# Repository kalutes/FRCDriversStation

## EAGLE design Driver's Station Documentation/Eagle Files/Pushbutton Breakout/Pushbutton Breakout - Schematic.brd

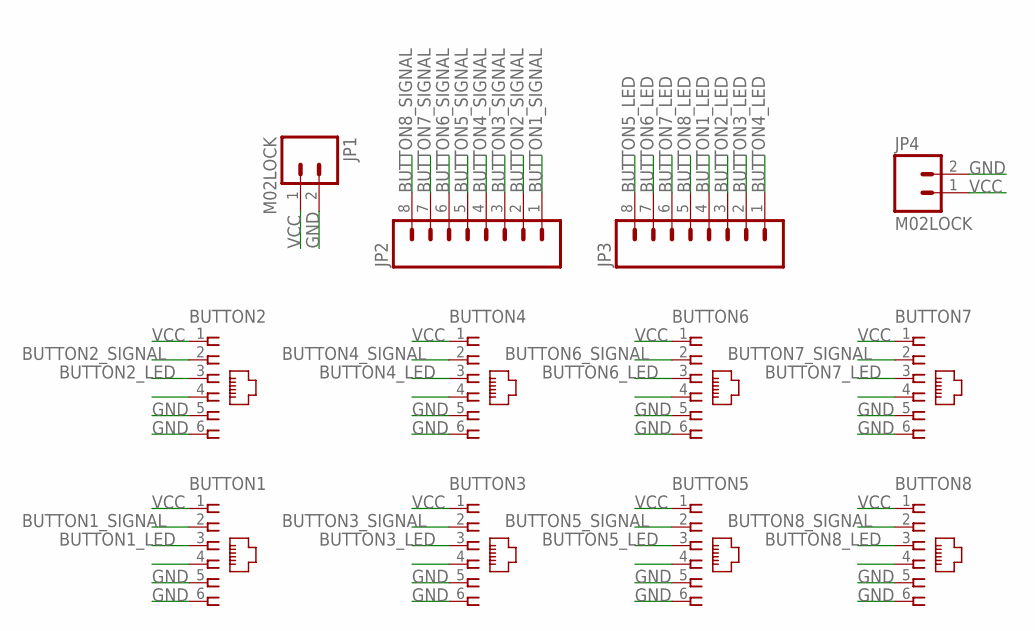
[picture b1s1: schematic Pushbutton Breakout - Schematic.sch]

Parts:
BUTTON1, BUTTON2, BUTTON3, BUTTON4, BUTTON5, BUTTON6, BUTTON7, BUTTON8: 555165-1
JP1, JP4: M02LOCK; 1X02_LOCK
JP2, JP3: M08LOCK; 1X08_LOCK

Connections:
BUTTON1_LED: BUTTON1.3, JP3.4
BUTTON1_SIGNAL: BUTTON1.2, JP2.1
BUTTON2_LED: BUTTON2.3, JP3.3
BUTTON2_SIGNAL: BUTTON2.2, JP2.2
BUTTON3_LED: BUTTON3.3, JP3.2
BUTTON3_SIGNAL: BUTTON3.2, JP2.3
BUTTON4_LED: BUTTON4.3, JP3.1
BUTTON4_SIGNAL: BUTTON4.2, JP2.4
BUTTON5_LED: BUTTON5.3, JP3.8
BUTTON5_SIGNAL: BUTTON5.2, JP2.5
BUTTON6_LED: BUTTON6.3, JP3.7
BUTTON6_SIGNAL: BUTTON6.2, JP2.6
BUTTON7_LED: BUTTON7.3, JP3.6
BUTTON7_SIGNAL: BUTTON7.2, JP2.7
BUTTON8_LED: BUTTON8.3, JP3.5
BUTTON8_SIGNAL: BUTTON8.2, JP2.8
GND: BUTTON1.5, BUTTON1.6, BUTTON2.5, BUTTON2.6, BUTTON3.5, BUTTON3.6, BUTTON4.5, BUTTON4.6, BUTTON5.5, BUTTON5.6, BUTTON6.5, BUTTON6.6, BUTTON7.5, BUTTON7.6, BUTTON8.5, BUTTON8.6, JP1.2, JP4.2
VCC: BUTTON1.1, BUTTON2.1, BUTTON3.1, BUTTON4.1, BUTTON5.1, BUTTON6.1, BUTTON7.1, BUTTON8.1, JP1.1, JP4.1

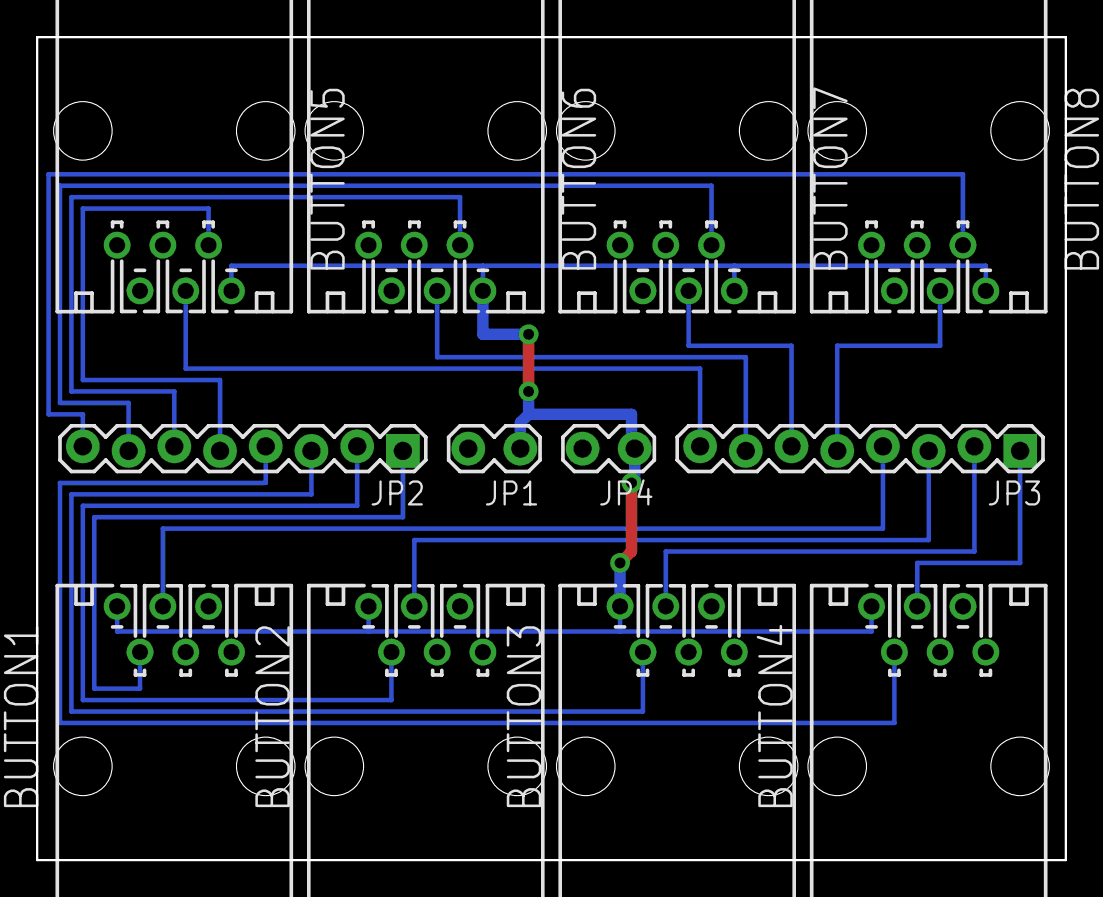
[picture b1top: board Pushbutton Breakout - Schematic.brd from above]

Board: 2 copper layers, 57.1 x 45.7 mm, 12 parts (0 on the bottom side), 18 nets.

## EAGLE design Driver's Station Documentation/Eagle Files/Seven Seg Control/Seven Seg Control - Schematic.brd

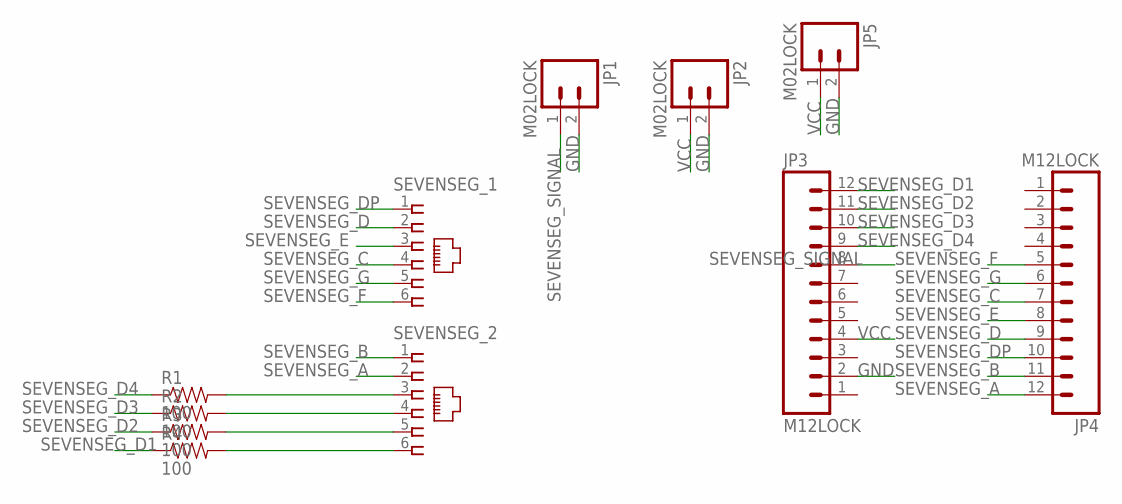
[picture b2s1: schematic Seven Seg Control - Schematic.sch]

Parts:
JP1, JP2, JP5: M02LOCK; 1X02_LOCK
JP3, JP4: M12LOCK; 1X12_LOCK
R1, R2, R3, R4: 100; 0603-RES
SEVENSEG_1, SEVENSEG_2: 555165-1

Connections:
GND: JP1.2, JP2.2, JP3.2, JP5.2
unnamed: R4.2, SEVENSEG_2.6
unnamed: R2.2, SEVENSEG_2.4
unnamed: R3.2, SEVENSEG_2.5
unnamed: R1.2, SEVENSEG_2.3
SEVENSEG_A: JP4.12, SEVENSEG_2.2
SEVENSEG_B: JP4.11, SEVENSEG_2.1
SEVENSEG_C: JP4.7, SEVENSEG_1.4
SEVENSEG_D: JP4.9, SEVENSEG_1.2
SEVENSEG_D1: JP3.12, R4.1
SEVENSEG_D2: JP3.11, R3.1
SEVENSEG_D3: JP3.10, R2.1
SEVENSEG_D4: JP3.9, R1.1
SEVENSEG_DP: JP4.10, SEVENSEG_1.1
SEVENSEG_E: JP4.8, SEVENSEG_1.3
SEVENSEG_F: JP4.5, SEVENSEG_1.6
SEVENSEG_G: JP4.6, SEVENSEG_1.5
SEVENSEG_SIGNAL: JP1.1, JP3.8
VCC: JP2.1, JP3.4, JP5.1

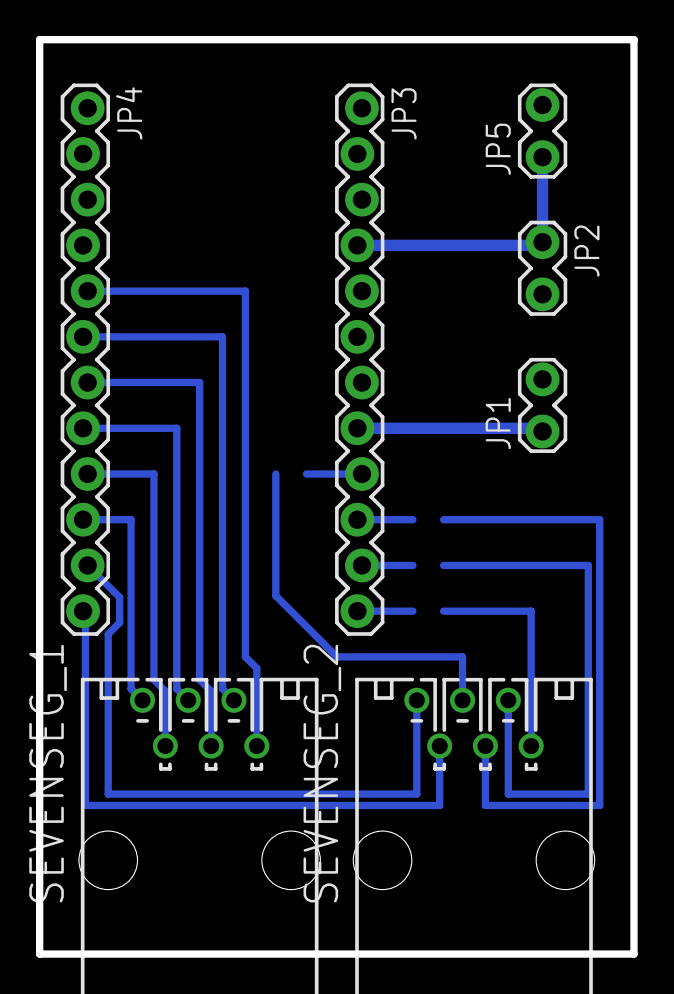
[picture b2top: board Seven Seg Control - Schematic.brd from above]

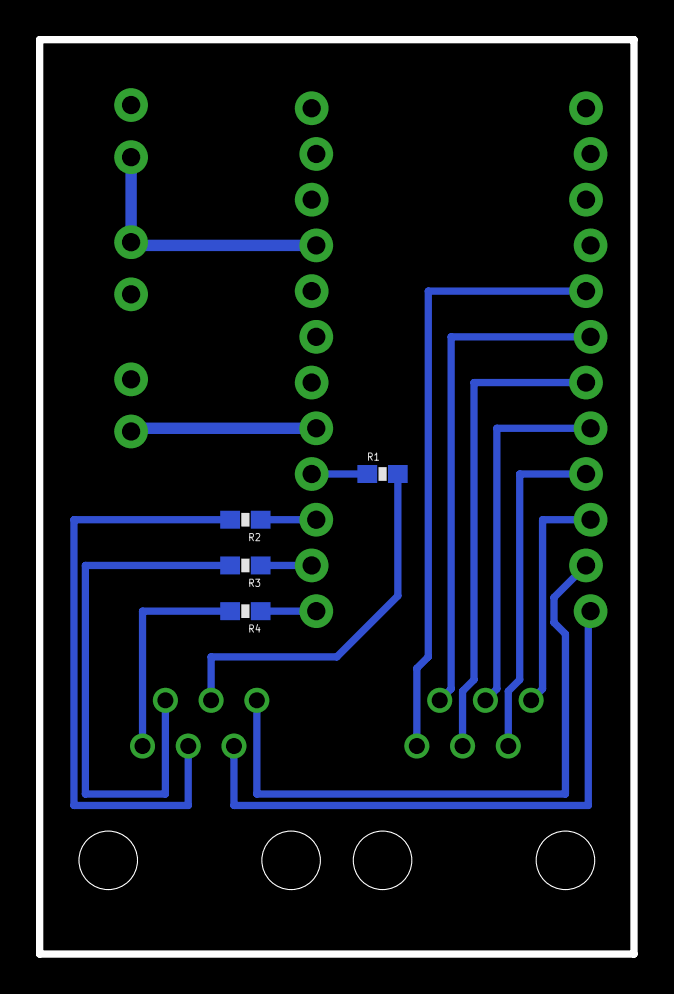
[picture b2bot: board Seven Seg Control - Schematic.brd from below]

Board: 2 copper layers, 33.0 x 50.8 mm, 11 parts (4 on the bottom side), 19 nets.

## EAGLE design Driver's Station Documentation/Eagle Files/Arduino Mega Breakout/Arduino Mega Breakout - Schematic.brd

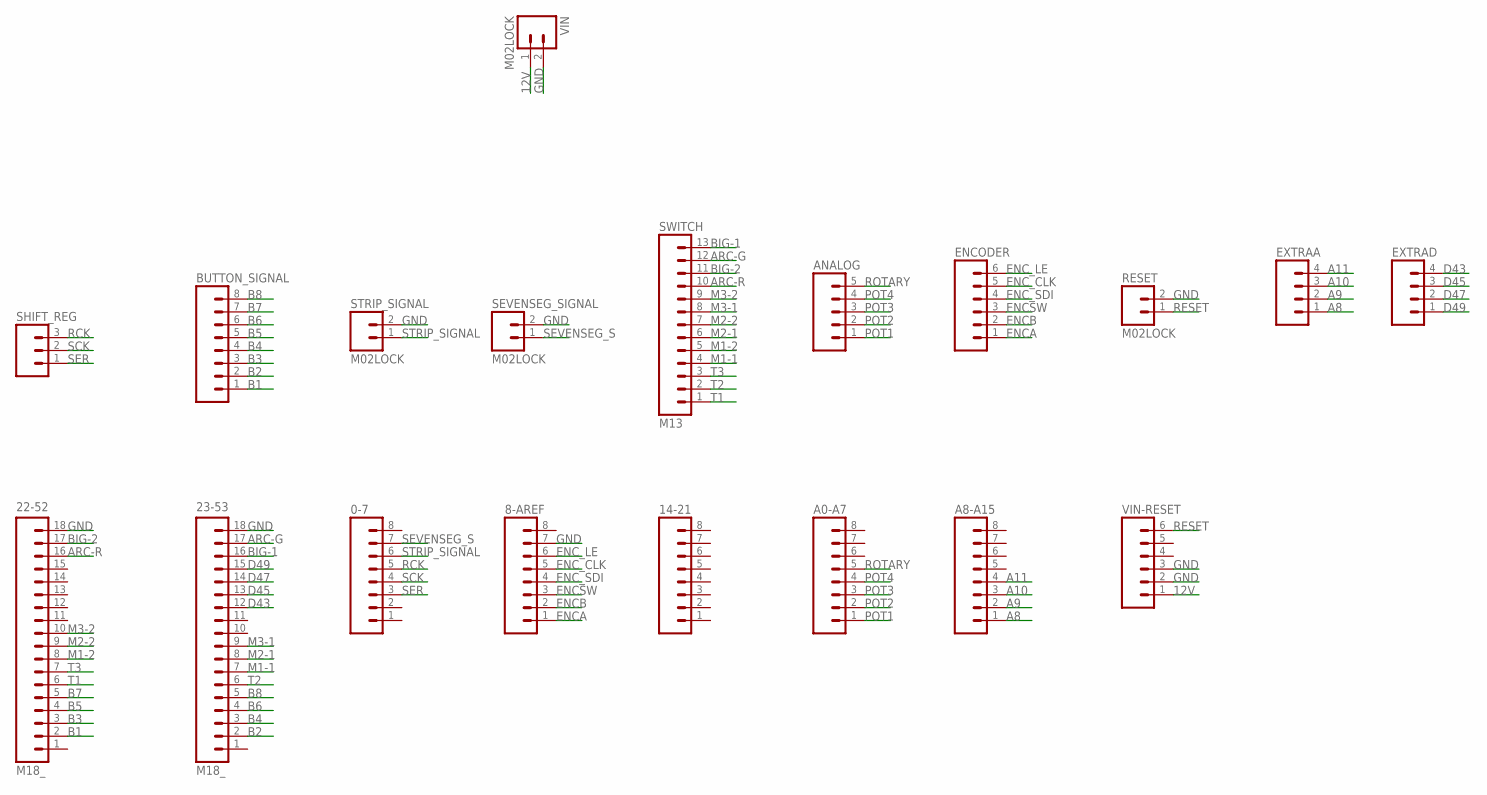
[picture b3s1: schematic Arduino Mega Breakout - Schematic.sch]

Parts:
0-7, 8-AREF, 14-21: M08LOCK; 1X08_LOCK
22-52, 23-53: M18_; 1X18
A0-A7, A8-A15: M08LOCK; 1X08_LOCK
ANALOG: M05LOCK; 1X05_LOCK
BUTTON_SIGNAL: M08; 1X08_PIN1_NO_SILK
ENCODER: M06LOCK; 1X06_LOCK
EXTRAA: M04LOCK; 1X04_LOCK
EXTRAD: M04PTH; 1X04
RESET: M02LOCK; 1X02_LOCK
SEVENSEG_SIGNAL: M02LOCK; 1X02_LOCK
SHIFT_REG: M03LOCK; 1X03_LOCK
STRIP_SIGNAL: M02LOCK; 1X02_LOCK
SWITCH: M13; 1X13
VIN: M02LOCK; 1X02_LOCK
VIN-RESET: M06LOCK; 1X06_LOCK

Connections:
12V: VIN.1, VIN-RESET.1
A8: A8-A15.1, EXTRAA.1
A9: A8-A15.2, EXTRAA.2
A10: A8-A15.3, EXTRAA.3
A11: A8-A15.4, EXTRAA.4
ARC-G: 23-53.17, SWITCH.12
ARC-R: 22-52.16, SWITCH.10
B1: 22-52.2, BUTTON_SIGNAL.1
B2: 23-53.2, BUTTON_SIGNAL.2
B3: 22-52.3, BUTTON_SIGNAL.3
B4: 23-53.3, BUTTON_SIGNAL.4
B5: 22-52.4, BUTTON_SIGNAL.5
B6: 23-53.4, BUTTON_SIGNAL.6
B7: 22-52.5, BUTTON_SIGNAL.7
B8: 23-53.5, BUTTON_SIGNAL.8
BIG-1: 23-53.16, SWITCH.13
BIG-2: 22-52.17, SWITCH.11
D43: 23-53.12, EXTRAD.4
D45: 23-53.13, EXTRAD.3
D47: 23-53.14, EXTRAD.2
D49: 23-53.15, EXTRAD.1
ENCA: 8-AREF.1, ENCODER.1
ENCB: 8-AREF.2, ENCODER.2
ENCSW: 8-AREF.3, ENCODER.3
ENC_CLK: 8-AREF.5, ENCODER.5
ENC_LE: 8-AREF.6, ENCODER.6
ENC_SDI: 8-AREF.4, ENCODER.4
GND: 8-AREF.7, 22-52.18, 23-53.18, RESET.2, SEVENSEG_SIGNAL.2, STRIP_SIGNAL.2, VIN.2, VIN-RESET.2, VIN-RESET.3
M1-1: 23-53.7, SWITCH.4
M1-2: 22-52.8, SWITCH.5
M2-1: 23-53.8, SWITCH.6
M2-2: 22-52.9, SWITCH.7
M3-1: 23-53.9, SWITCH.8
M3-2: 22-52.10, SWITCH.9
POT1: A0-A7.1, ANALOG.1
POT2: A0-A7.2, ANALOG.2
POT3: A0-A7.3, ANALOG.3
POT4: A0-A7.4, ANALOG.4
RCK: 0-7.5, SHIFT_REG.3
RESET: RESET.1, VIN-RESET.6
ROTARY: A0-A7.5, ANALOG.5
SCK: 0-7.4, SHIFT_REG.2
SER: 0-7.3, SHIFT_REG.1
SEVENSEG_S: 0-7.7, SEVENSEG_SIGNAL.1
STRIP_SIGNAL: 0-7.6, STRIP_SIGNAL.1
T1: 22-52.6, SWITCH.1
T2: 23-53.6, SWITCH.2
T3: 22-52.7, SWITCH.3

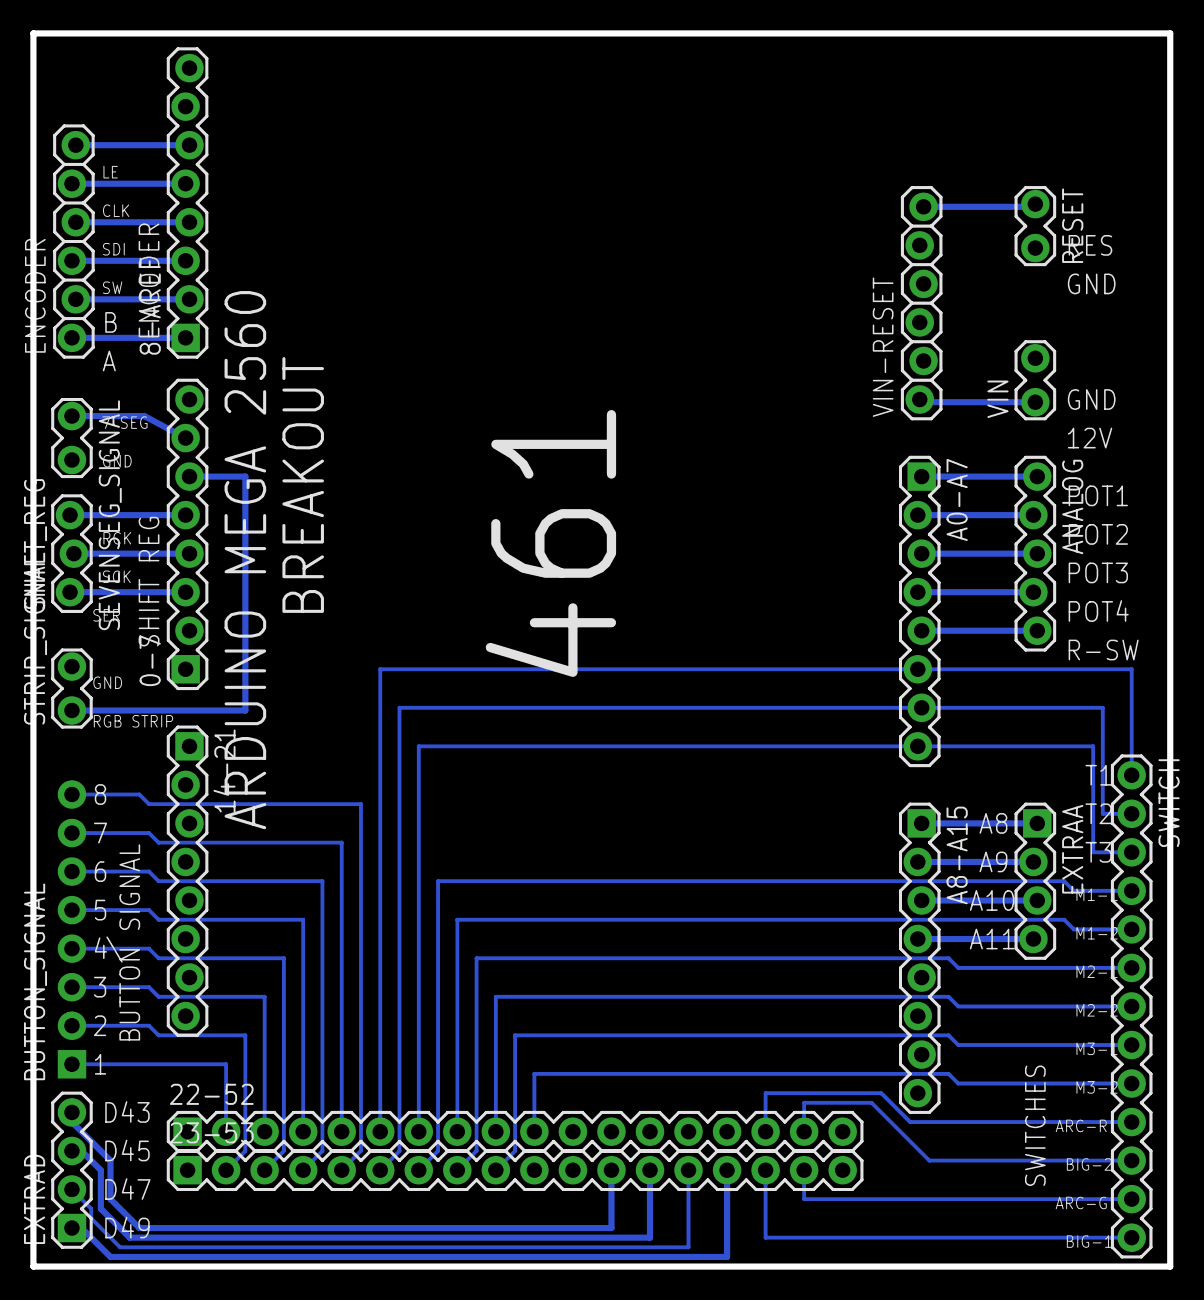
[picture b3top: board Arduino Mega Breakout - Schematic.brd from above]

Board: 2 copper layers, 74.9 x 81.3 mm, 19 parts (0 on the bottom side), 48 nets.

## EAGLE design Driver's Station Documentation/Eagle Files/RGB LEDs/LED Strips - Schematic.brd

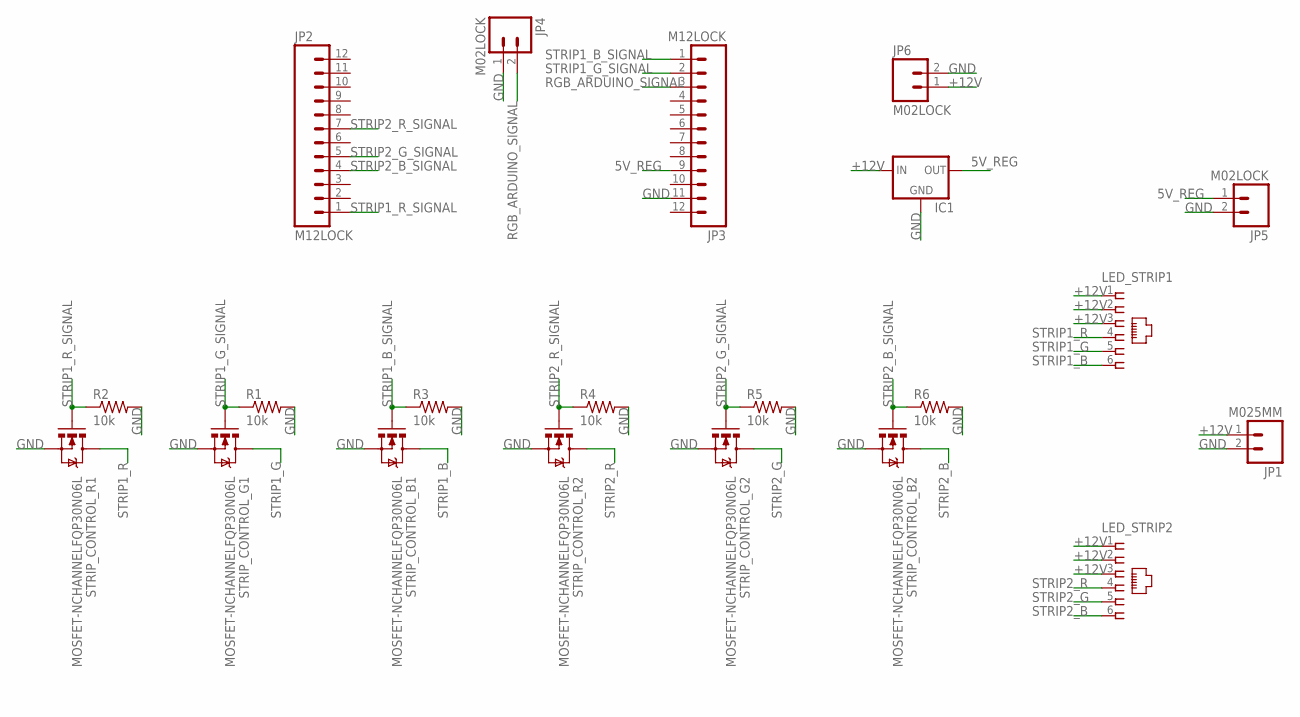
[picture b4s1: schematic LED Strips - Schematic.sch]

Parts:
IC1: V_REG_78XXSIDE; 78XXL
JP1: M025MM; SCREWTERMINAL-5MM-2
JP2, JP3: M12LOCK; 1X12_LOCK
JP4, JP5, JP6: M02LOCK; 1X02_LOCK
LED_STRIP1, LED_STRIP2: 555165-1
R1, R2, R3, R4, R5, R6: 10k; 0603-RES
STRIP_CONTROL_B1, STRIP_CONTROL_B2: MOSFET-NCHANNELFQP30N06L; TO220V
STRIP_CONTROL_G1, STRIP_CONTROL_G2: MOSFET-NCHANNELFQP30N06L; TO220V
STRIP_CONTROL_R1, STRIP_CONTROL_R2: MOSFET-NCHANNELFQP30N06L; TO220V

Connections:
5V_REG: IC1.OUT, JP3.9, JP5.1
+12V: IC1.IN, JP1.1, JP6.1, LED_STRIP1.1, LED_STRIP1.2, LED_STRIP1.3, LED_STRIP2.1, LED_STRIP2.2, LED_STRIP2.3
GND: IC1.GND, JP1.2, JP3.11, JP4.1, JP5.2, JP6.2, R1.2, R2.2, R3.2, R4.2, R5.2, R6.2, STRIP_CONTROL_B1.3 (S), STRIP_CONTROL_B2.3 (S), STRIP_CONTROL_G1.3 (S), STRIP_CONTROL_G2.3 (S), STRIP_CONTROL_R1.3 (S), STRIP_CONTROL_R2.3 (S)
RGB_ARDUINO_SIGNAL: JP3.3, JP4.2
STRIP1_B: LED_STRIP1.6, STRIP_CONTROL_B1.2 (D)
STRIP1_B_SIGNAL: JP3.1, R3.1, STRIP_CONTROL_B1.1 (G)
STRIP1_G: LED_STRIP1.5, STRIP_CONTROL_G1.2 (D)
STRIP1_G_SIGNAL: JP3.2, R1.1, STRIP_CONTROL_G1.1 (G)
STRIP1_R: LED_STRIP1.4, STRIP_CONTROL_R1.2 (D)
STRIP1_R_SIGNAL: JP2.1, R2.1, STRIP_CONTROL_R1.1 (G)
STRIP2_B: LED_STRIP2.6, STRIP_CONTROL_B2.2 (D)
STRIP2_B_SIGNAL: JP2.4, R6.1, STRIP_CONTROL_B2.1 (G)
STRIP2_G: LED_STRIP2.5, STRIP_CONTROL_G2.2 (D)
STRIP2_G_SIGNAL: JP2.5, R5.1, STRIP_CONTROL_G2.1 (G)
STRIP2_R: LED_STRIP2.4, STRIP_CONTROL_R2.2 (D)
STRIP2_R_SIGNAL: JP2.7, R4.1, STRIP_CONTROL_R2.1 (G)

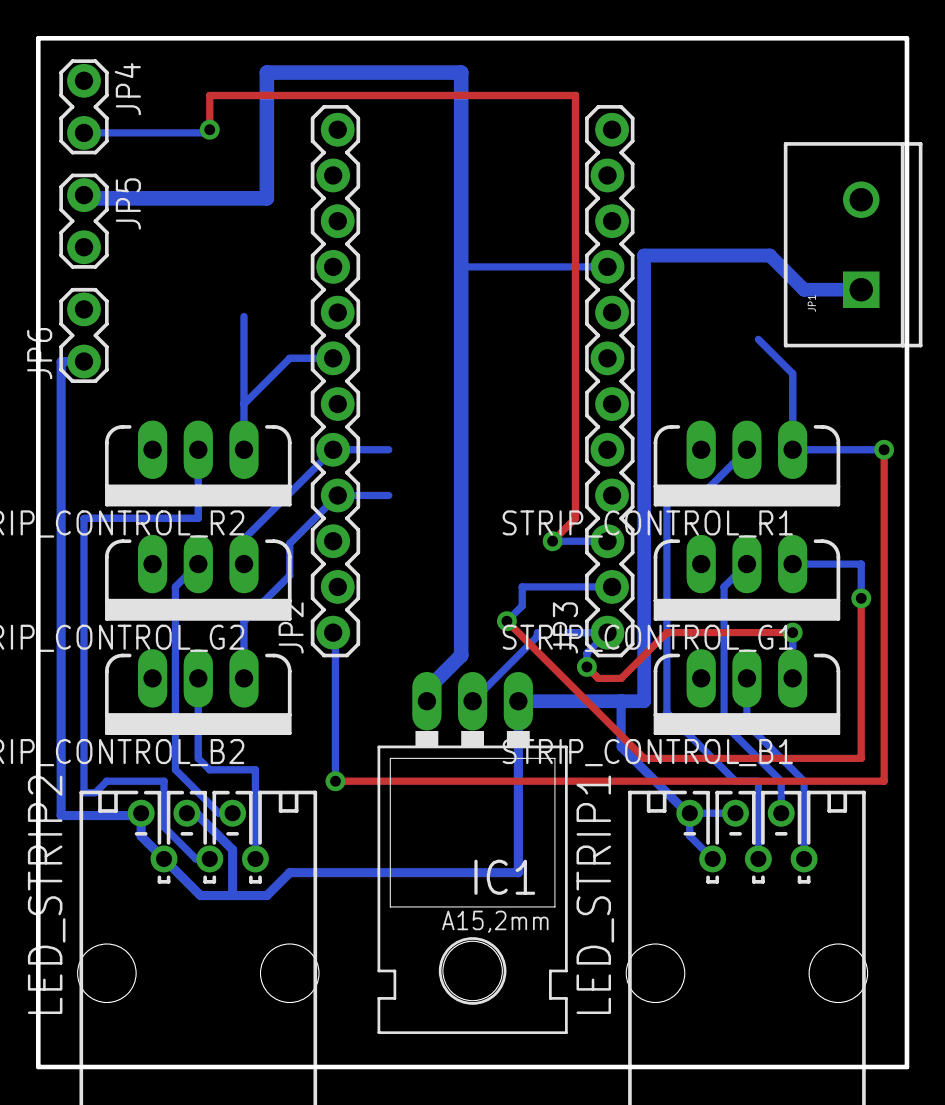
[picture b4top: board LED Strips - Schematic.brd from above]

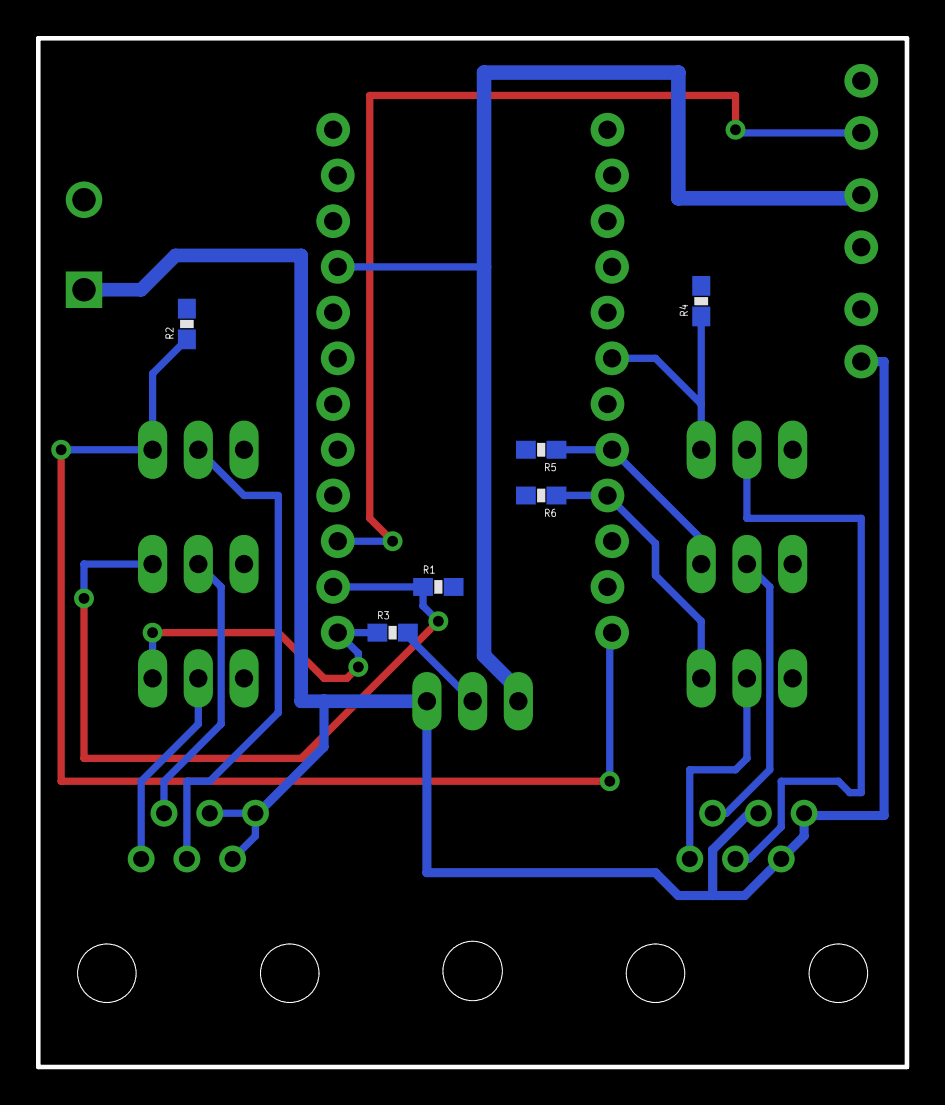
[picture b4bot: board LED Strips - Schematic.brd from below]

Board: 2 copper layers, 48.3 x 57.1 mm, 21 parts (6 on the bottom side), 16 nets.

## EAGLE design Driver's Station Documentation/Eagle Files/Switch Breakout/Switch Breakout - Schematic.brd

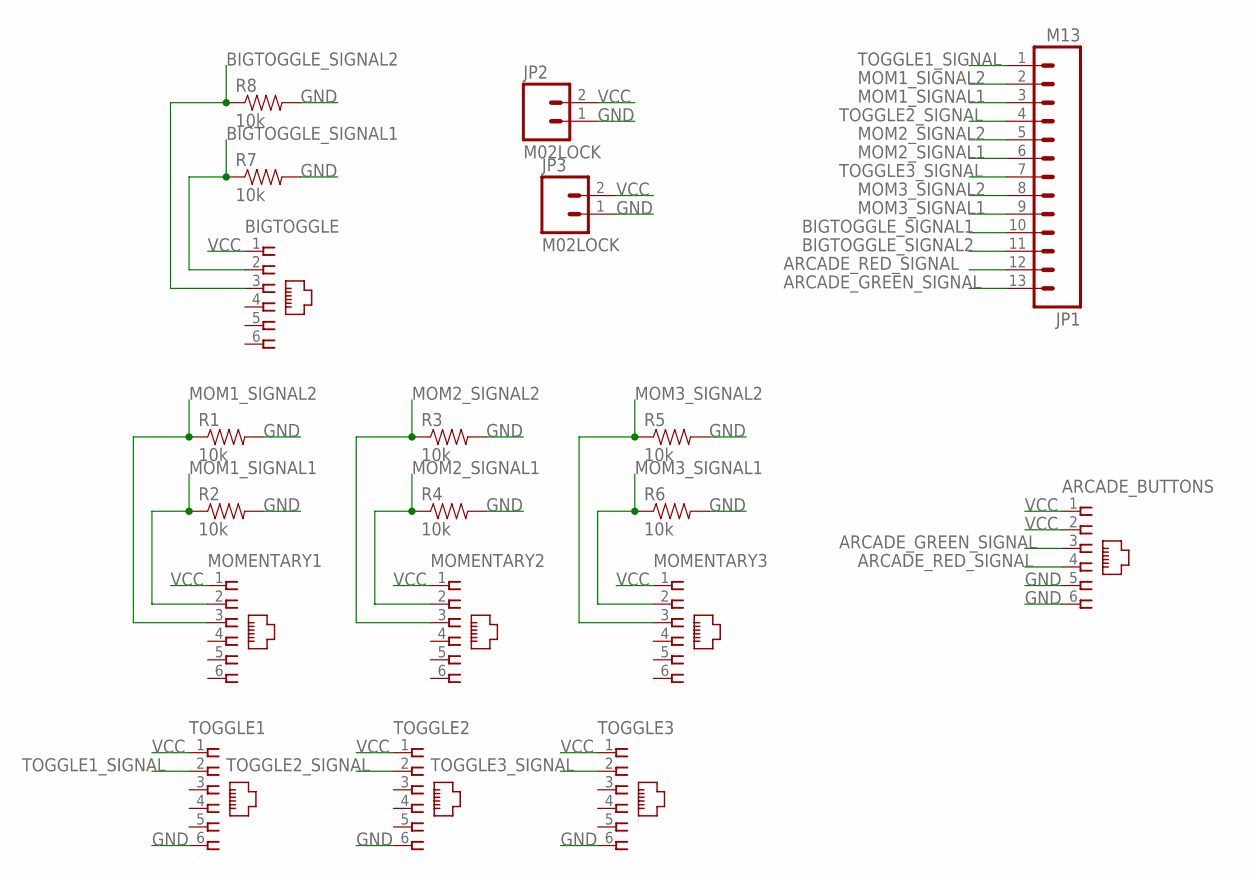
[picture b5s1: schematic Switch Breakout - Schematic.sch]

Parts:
ARCADE_BUTTONS: 555165-1
BIGTOGGLE: 555165-1
JP1: M13; 1X13
JP2, JP3: M02LOCK; 1X02_LOCK
MOMENTARY1, MOMENTARY2, MOMENTARY3: 555165-1
R1, R2, R3, R4, R5, R6, R7, R8: 10k; 0603-RES
TOGGLE1, TOGGLE2, TOGGLE3: 555165-1

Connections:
ARCADE_GREEN_SIGNAL: ARCADE_BUTTONS.3, JP1.13
ARCADE_RED_SIGNAL: ARCADE_BUTTONS.4, JP1.12
BIGTOGGLE_SIGNAL1: BIGTOGGLE.2, JP1.10, R7.1
BIGTOGGLE_SIGNAL2: BIGTOGGLE.3, JP1.11, R8.1
GND: ARCADE_BUTTONS.5, ARCADE_BUTTONS.6, JP2.1, JP3.1, R1.2, R2.2, R3.2, R4.2, R5.2, R6.2, R7.2, R8.2, TOGGLE1.6, TOGGLE2.6, TOGGLE3.6
MOM1_SIGNAL1: JP1.3, MOMENTARY1.2, R2.1
MOM1_SIGNAL2: JP1.2, MOMENTARY1.3, R1.1
MOM2_SIGNAL1: JP1.6, MOMENTARY2.2, R4.1
MOM2_SIGNAL2: JP1.5, MOMENTARY2.3, R3.1
MOM3_SIGNAL1: JP1.9, MOMENTARY3.2, R6.1
MOM3_SIGNAL2: JP1.8, MOMENTARY3.3, R5.1
TOGGLE1_SIGNAL: JP1.1, TOGGLE1.2
TOGGLE2_SIGNAL: JP1.4, TOGGLE2.2
TOGGLE3_SIGNAL: JP1.7, TOGGLE3.2
VCC: ARCADE_BUTTONS.1, ARCADE_BUTTONS.2, BIGTOGGLE.1, JP2.2, JP3.2, MOMENTARY1.1, MOMENTARY2.1, MOMENTARY3.1, TOGGLE1.1, TOGGLE2.1, TOGGLE3.1

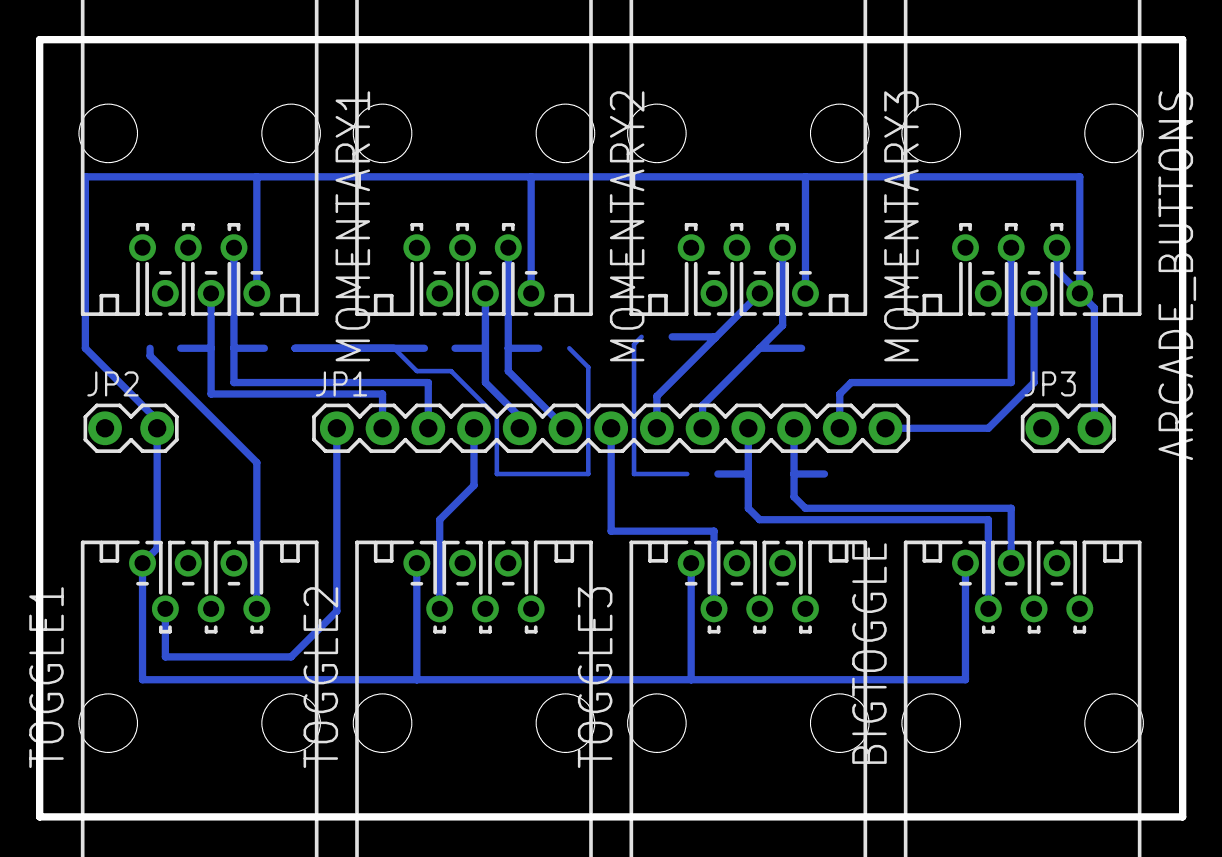
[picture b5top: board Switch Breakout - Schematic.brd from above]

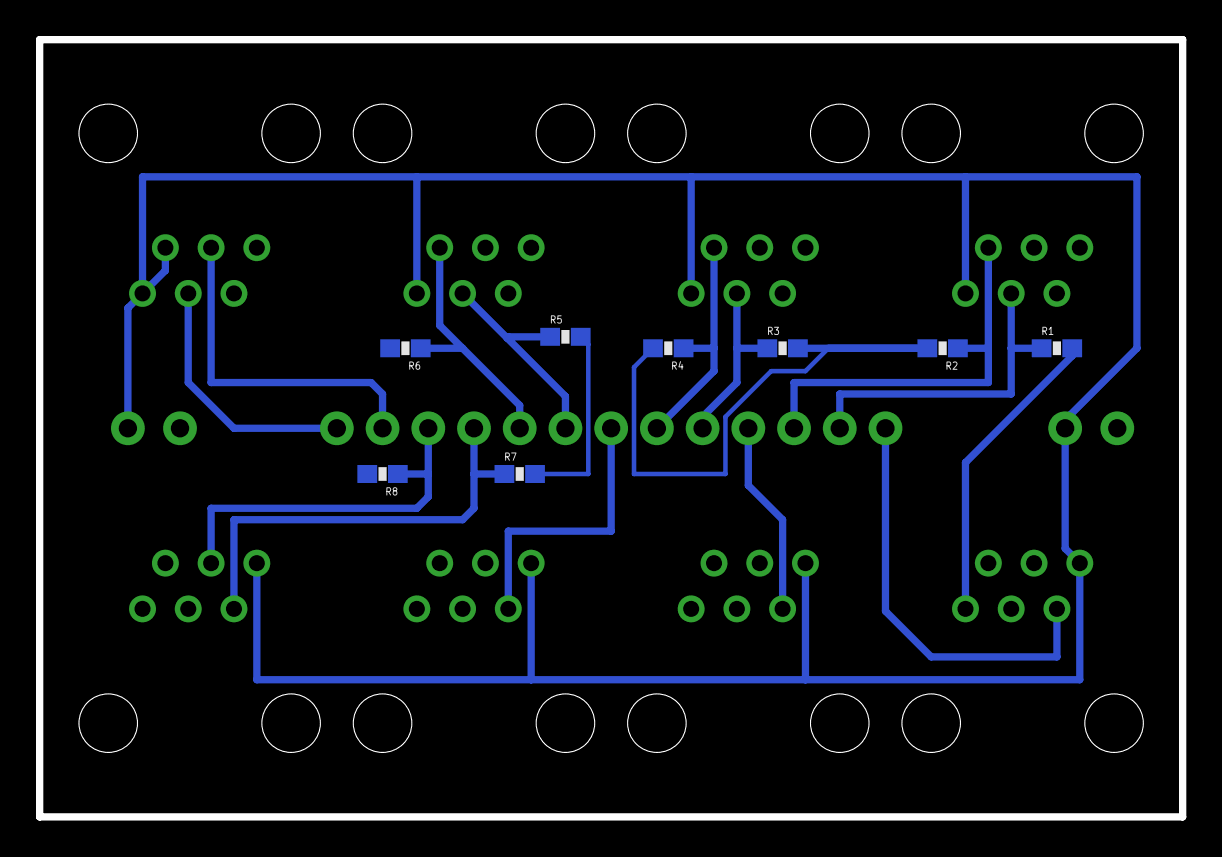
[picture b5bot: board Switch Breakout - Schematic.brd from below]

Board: 2 copper layers, 63.5 x 43.2 mm, 19 parts (8 on the bottom side), 15 nets.

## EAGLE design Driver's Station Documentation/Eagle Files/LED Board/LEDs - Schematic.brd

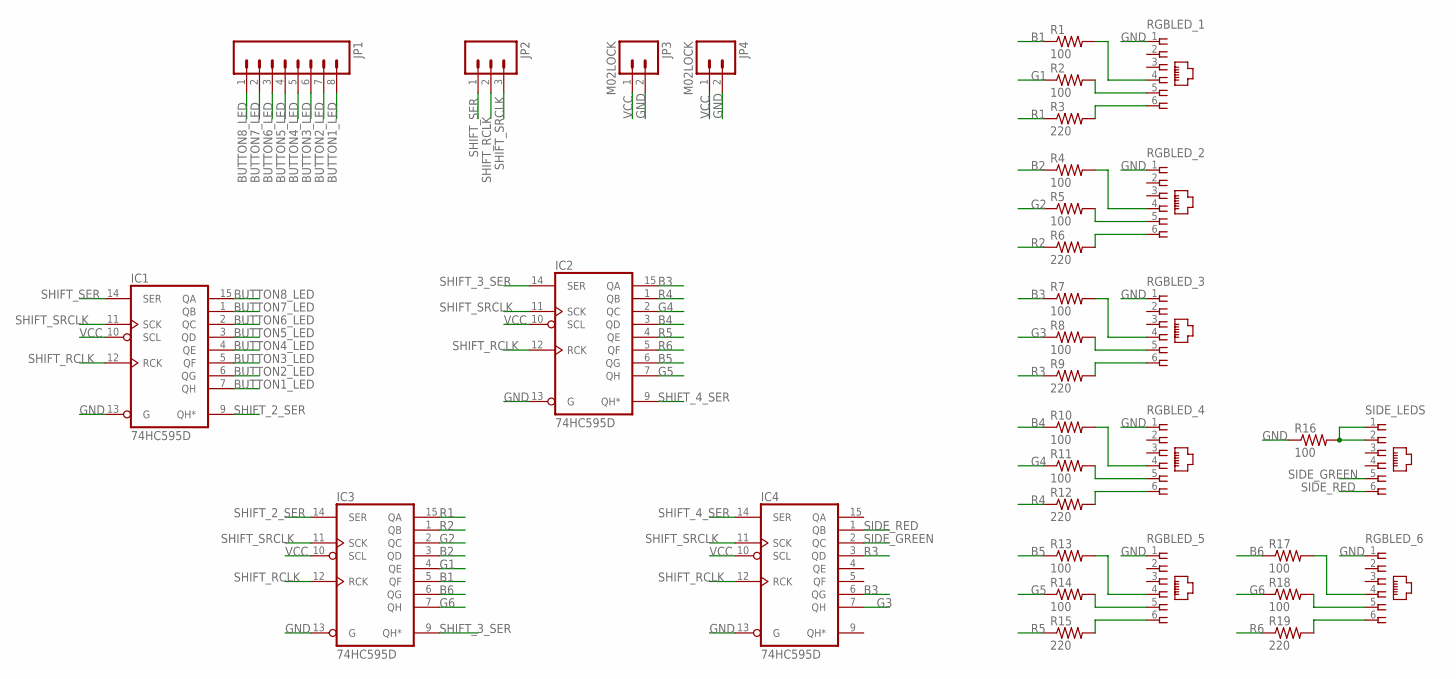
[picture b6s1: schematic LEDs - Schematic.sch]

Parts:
IC1, IC2, IC3, IC4: 74HC595D; SO16
JP1: M08LOCK; 1X08_LOCK
JP2: M03LOCK; 1X03_LOCK
JP3, JP4: M02LOCK; 1X02_LOCK
R1, R2, R4, R5, R7, R8, R10, R11, R13, R14, R16, R17, R18: 100; 0603-RES
R3, R6, R9, R12, R15, R19: 220; 0603-RES
RGBLED_1, RGBLED_2, RGBLED_3, RGBLED_4, RGBLED_5, RGBLED_6: 555165-1
SIDE_LEDS: 555165-1

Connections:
B1: IC3.5 (QF), R1.1
B2: IC3.3 (QD), R4.1
B3: IC2.15 (QA), IC4.6 (QG), R7.1
B4: IC2.3 (QD), R10.1
B5: IC2.6 (QG), R13.1
B6: IC3.6 (QG), R17.1
BUTTON1_LED: IC1.7 (QH), JP1.8
BUTTON2_LED: IC1.6 (QG), JP1.7
BUTTON3_LED: IC1.5 (QF), JP1.6
BUTTON4_LED: IC1.4 (QE), JP1.5
BUTTON5_LED: IC1.3 (QD), JP1.4
BUTTON6_LED: IC1.2 (QC), JP1.3
BUTTON7_LED: IC1.1 (QB), JP1.2
BUTTON8_LED: IC1.15 (QA), JP1.1
G1: IC3.4 (QE), R2.1
G2: IC3.2 (QC), R5.1
G3: IC4.7 (QH), R8.1
G4: IC2.2 (QC), R11.1
G5: IC2.7 (QH), R14.1
G6: IC3.7 (QH), R18.1
GND: IC1.8 (GND), IC1.13 (G), IC2.8 (GND), IC2.13 (G), IC3.8 (GND), IC3.13 (G), IC4.8 (GND), IC4.13 (G), JP3.2, JP4.2, R16.1, RGBLED_1.1, RGBLED_2.1, RGBLED_3.1, RGBLED_4.1, RGBLED_5.1, RGBLED_6.1
unnamed: R1.2, RGBLED_1.4
unnamed: R2.2, RGBLED_1.5
unnamed: R3.2, RGBLED_1.6
unnamed: R4.2, RGBLED_2.4
unnamed: R5.2, RGBLED_2.5
unnamed: R6.2, RGBLED_2.6
unnamed: R7.2, RGBLED_3.4
unnamed: R8.2, RGBLED_3.5
unnamed: R9.2, RGBLED_3.6
unnamed: R10.2, RGBLED_4.4
unnamed: R11.2, RGBLED_4.5
unnamed: R12.2, RGBLED_4.6
unnamed: R13.2, RGBLED_5.4
unnamed: R14.2, RGBLED_5.5
unnamed: R15.2, RGBLED_5.6
unnamed: R17.2, RGBLED_6.4
unnamed: R18.2, RGBLED_6.5
unnamed: R19.2, RGBLED_6.6
unnamed: R16.2, SIDE_LEDS.1, SIDE_LEDS.2
R1: IC3.15 (QA), R3.1
R2: IC3.1 (QB), R6.1
R3: IC4.3 (QD), R9.1
R4: IC2.1 (QB), R12.1
R5: IC2.4 (QE), R15.1
R6: IC2.5 (QF), R19.1
SHIFT_2_SER: IC1.9 (QH*), IC3.14 (SER)
SHIFT_3_SER: IC2.14 (SER), IC3.9 (QH*)
SHIFT_4_SER: IC2.9 (QH*), IC4.14 (SER)
SHIFT_RCLK: IC1.12 (RCK), IC2.12 (RCK), IC3.12 (RCK), IC4.12 (RCK), JP2.2
SHIFT_SER: IC1.14 (SER), JP2.1
SHIFT_SRCLK: IC1.11 (SCK), IC2.11 (SCK), IC3.11 (SCK), IC4.11 (SCK), JP2.3
SIDE_GREEN: IC4.2 (QC), SIDE_LEDS.5
SIDE_RED: IC4.1 (QB), SIDE_LEDS.6
VCC: IC1.10 (SCL), IC1.16 (VCC), IC2.10 (SCL), IC2.16 (VCC), IC3.10 (SCL), IC3.16 (VCC), IC4.10 (SCL), IC4.16 (VCC), JP3.1, JP4.1

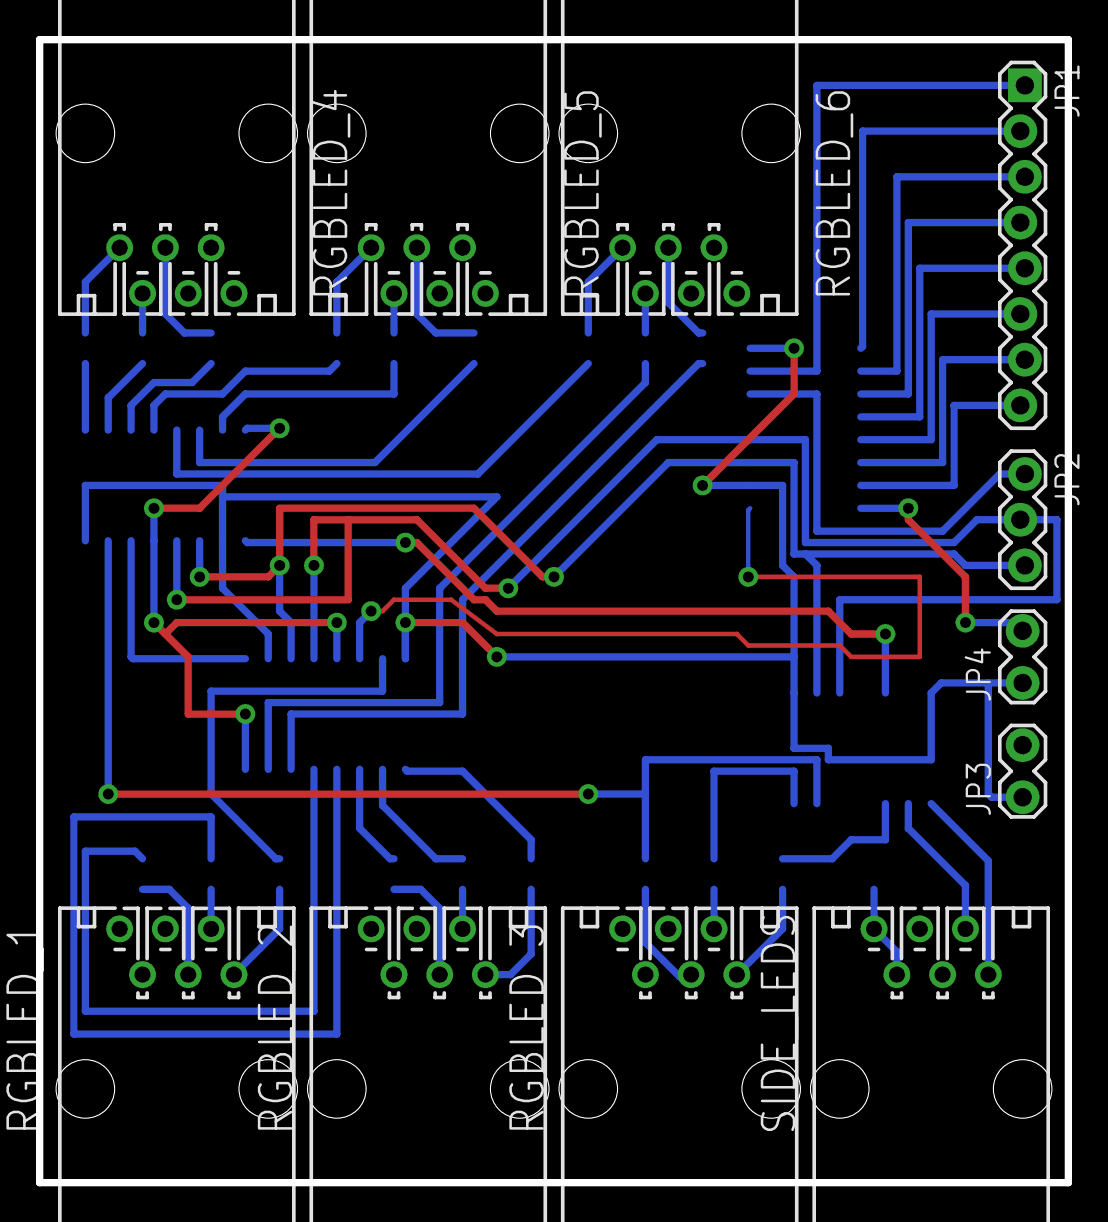
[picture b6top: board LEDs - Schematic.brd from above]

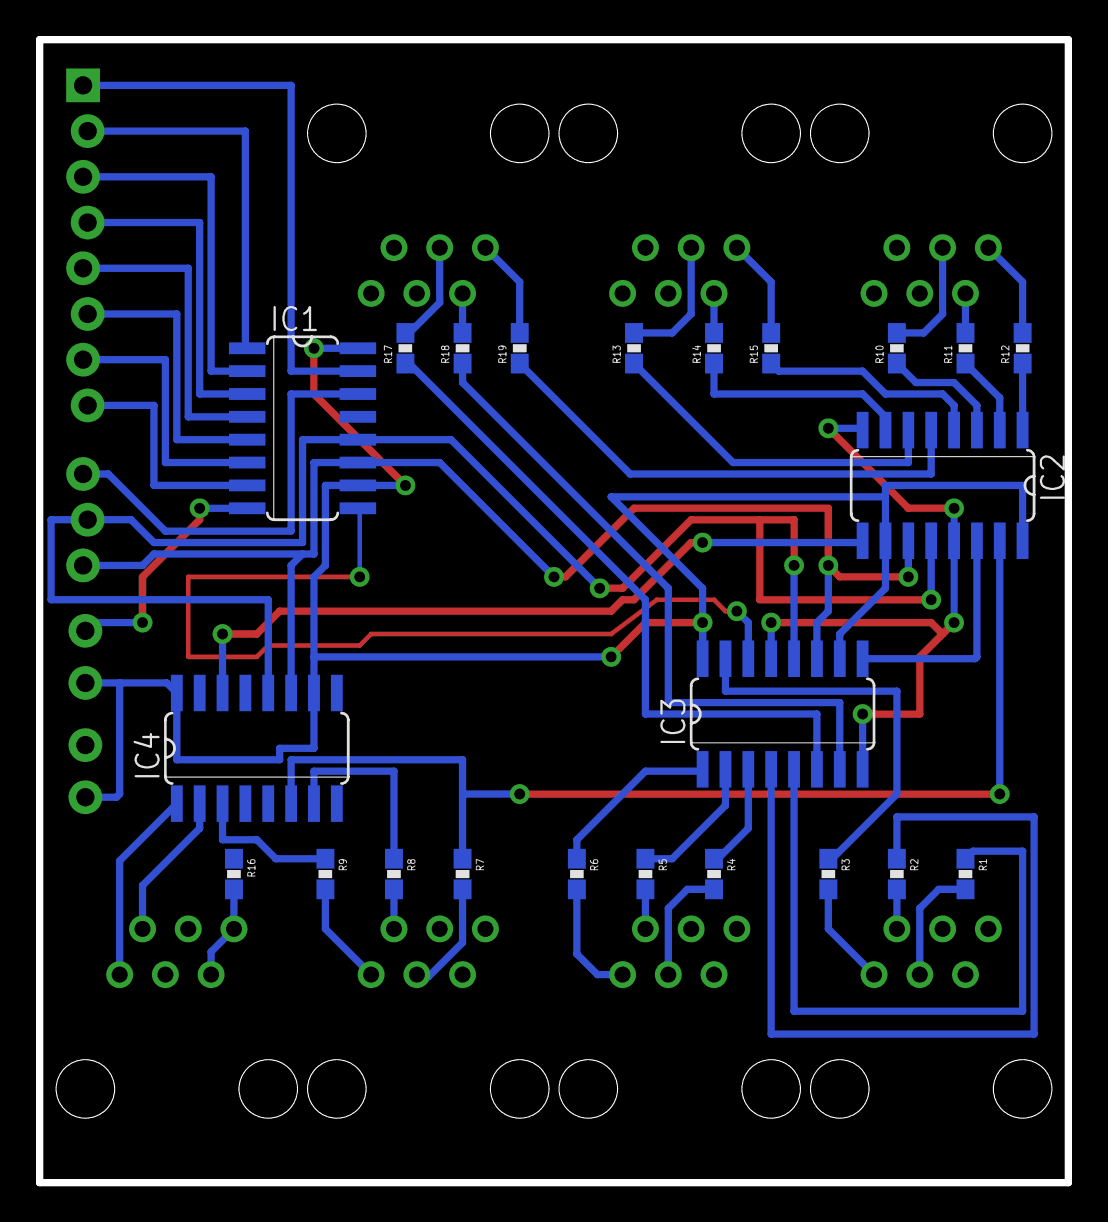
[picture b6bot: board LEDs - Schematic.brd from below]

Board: 2 copper layers, 57.1 x 63.5 mm, 34 parts (23 on the bottom side), 55 nets.

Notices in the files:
parts and their libraries:
SparkFun-Connectors: Licensing: Creative Commons ShareAlike 4.0 International - https://creativecommons.org/licenses/by-sa/4.0
